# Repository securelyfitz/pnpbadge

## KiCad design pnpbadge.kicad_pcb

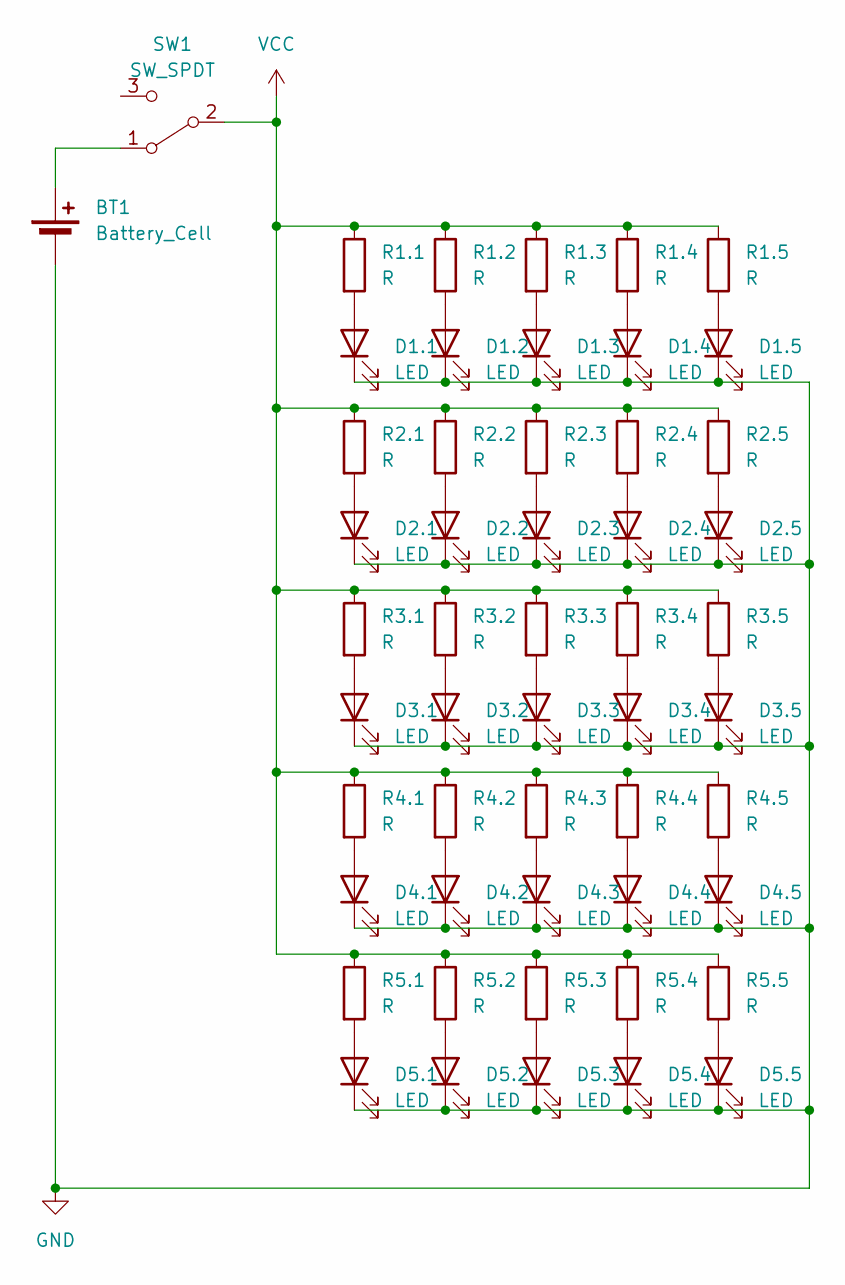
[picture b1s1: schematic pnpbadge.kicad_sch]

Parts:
BT1: Battery_Cell; BatteryHolder_MPD_BC2003_1x2032
D1.1, D1.2, D1.3, D1.4, D1.5, D2.1, D2.2, D2.3, D2.4, D2.5, D3.1, D3.2, D3.3, D3.4, D3.5, D4.1, D4.2, D4.3, D4.4, D4.5, D5.1, D5.2, D5.3, D5.4, D5.5: LED; LED_0603_1608Metric
R1.1, R1.2, R1.3, R1.4, R1.5, R2.1, R2.2, R2.3, R2.4, R2.5, R3.1, R3.2, R3.3, R3.4, R3.5, R4.1, R4.2, R4.3, R4.4, R4.5, R5.1, R5.2, R5.3, R5.4, R5.5: R; R_0603_1608Metric
SW1: SW_SPDT; SW_SPDT_PCM12

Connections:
GND: BT1.2 (-), D1.1.1 (K), D1.2.1 (K), D1.3.1 (K), D1.4.1 (K), D1.5.1 (K), D2.1.1 (K), D2.2.1 (K), D2.3.1 (K), D2.4.1 (K), D2.5.1 (K), D3.1.1 (K), D3.2.1 (K), D3.3.1 (K), D3.4.1 (K), D3.5.1 (K), D4.1.1 (K), D4.2.1 (K), D4.3.1 (K), D4.4.1 (K), D4.5.1 (K), D5.1.1 (K), D5.2.1 (K), D5.3.1 (K), D5.4.1 (K), D5.5.1 (K)
unnamed: BT1.1 (+), SW1.1 (A)
unnamed: D1.1.2 (A), R1.1.2
unnamed: D1.2.2 (A), R1.2.2
unnamed: D1.3.2 (A), R1.3.2
unnamed: D1.4.2 (A), R1.4.2
unnamed: D1.5.2 (A), R1.5.2
unnamed: D2.1.2 (A), R2.1.2
unnamed: D2.2.2 (A), R2.2.2
unnamed: D2.3.2 (A), R2.3.2
unnamed: D2.4.2 (A), R2.4.2
unnamed: D2.5.2 (A), R2.5.2
unnamed: D3.1.2 (A), R3.1.2
unnamed: D3.2.2 (A), R3.2.2
unnamed: D3.3.2 (A), R3.3.2
unnamed: D3.4.2 (A), R3.4.2
unnamed: D3.5.2 (A), R3.5.2
unnamed: D4.1.2 (A), R4.1.2
unnamed: D4.2.2 (A), R4.2.2
unnamed: D4.3.2 (A), R4.3.2
unnamed: D4.4.2 (A), R4.4.2
unnamed: D4.5.2 (A), R4.5.2
unnamed: D5.1.2 (A), R5.1.2
unnamed: D5.2.2 (A), R5.2.2
unnamed: D5.3.2 (A), R5.3.2
unnamed: D5.4.2 (A), R5.4.2
unnamed: D5.5.2 (A), R5.5.2
VCC: R1.1.1, R1.2.1, R1.3.1, R1.4.1, R1.5.1, R2.1.1, R2.2.1, R2.3.1, R2.4.1, R2.5.1, R3.1.1, R3.2.1, R3.3.1, R3.4.1, R3.5.1, R4.1.1, R4.2.1, R4.3.1, R4.4.1, R4.5.1, R5.1.1, R5.2.1, R5.3.1, R5.4.1, R5.5.1, SW1.2 (B)

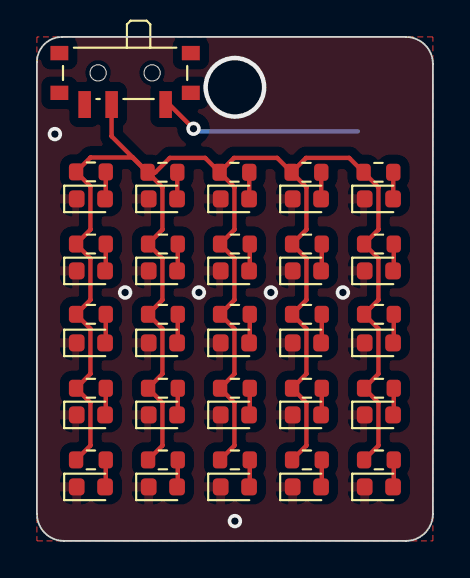
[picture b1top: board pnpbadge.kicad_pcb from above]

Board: 2 copper layers, 22.0 x 28.0 mm, 52 parts (1 on the bottom side), 28 nets.

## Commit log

2023-06-15 first rev of 5x5 led badge for pnp practice
